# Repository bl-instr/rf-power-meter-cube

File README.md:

# RF Power Meter Cube

**Compact, wireless RF power measurement for distributed instrumentation and Blinky-Lite control-system deployments.**

| Enclosure | PCB |
|-----------|-----|
||

## Overview

The RF Power Meter Cube is a compact, wireless instrumentation module in the Blinky-Lite Instrumentation Platform. It is designed to measure RF power at or near the equipment being monitored, then communicate measurements and alarms to a central Blinky-Lite control system.

Built around the Raspberry Pi Pico W / RP2040, the module uses 2.4 GHz Wi-Fi and MQTT publish/subscribe communication. This event-driven approach supports distributed deployments without wired data connections and enables Blinky-Lite to use device information for recording, notifications, visualisation, and machine-protection workflows.

### Key features

- Purpose-built function: Dedicated RF power measurement using the Mini-Circuits ZX47-40LN-S+ logarithmic RF power detector.
- Compact deployment: DIN Mod3-compatible enclosure with a removable DIN-rail mount for space-constrained installations.
- Wireless connectivity: 2.4 GHz Wi-Fi for remote or distributed installations.
- Event-driven integration: MQTT publish/subscribe communication with Blinky-Lite.
- Fast alarm and state reporting: RF power exceeding or falling below configured limits can be reported immediately.
- Configurable operation: Using the Blinky-Lite control system, calibration constants can be adjusted easily for each device and its particular frequency band.
- Open-source firmware: Microcontroller code can be adapted for site-specific instrumentation and integration requirements.

## Technical summary

| Specification | Details |
|---------------|---------|
| Primary function | RF power measurement |
| Sensor / interface | Mini-Circuits ZX47-40LN-S+ RF power detector |
| Channels | One RF measurement channel |
| Measurement / operating range | 10 MHz to 8 GHz; 60 dB dynamic range (−40 dBm to +20 dBm) |
| Inputs / outputs | SMA male RF input |
| Power input | 5 V DC via 2.1 mm barrel connector |
| Wireless | 2.4 GHz Wi-Fi |
| Communication | MQTT publish/subscribe protocol |
| Controller | Raspberry Pi Pico W / RP2040 |
| PCB dimensions | 48 mm × 86 mm |
| Enclosure and mounting | 58 mm × 96 mm × 28 mm; DIN Mod3-compatible enclosure with removable DIN-rail mount |
| Platform | Blinky-Lite Instrumentation Platform |

### Typical applications

- RF system commissioning and troubleshooting
- Continuous RF power monitoring at remote equipment locations
- Accelerator, laboratory, and industrial test systems
- Distributed instrumentation installations requiring central visibility
- RF alarm and machine-protection workflows

## Getting started

### Hardware

1. Install the RF Power Meter Cube near the RF point to be monitored.
2. Connect the RF signal to the SMA input, ensuring the expected input level and frequency remain within the supported measurement range.
3. Verify that the RF source, connector, cabling, and installation conditions are suitable for the application.
4. Power the device from a regulated 5 V DC supply through the 2.1 mm barrel connector.
5. Mount the enclosure on a DIN rail when required, or remove the DIN-rail mount for an alternative installation.

### Firmware build target

The firmware targets the Raspberry Pi Pico W / RP2040 using the Arduino-Pico board support.
- Board: Pico W / RP2040-compatible target
- Flash layout: Sketch 1920 KB, filesystem 128 KB
- FQBN flash option: flash=2097152_131072

### Open-source software and licensing

The firmware is released under the MIT License, giving users broad permission to study, modify, and adapt the code for their own applications. The open hardware design can likewise be customised to suit site-specific requirements. The firmware uses the open-source Arduino-BlinkyPicoW library, which is also available under the MIT License.

### Configuration

1. Build and upload the firmware using the project’s source and configuration files.
2. Use the onboard web interface to set or update Wi-Fi credentials.
3. Configure the MQTT connection and create the corresponding device integration in Blinky-Lite.
4. Set calibration data and measurement limits appropriate to the RF detector, operating frequency, and required accuracy.
5. Verify that normal measurements and alarm events appear as expected in Blinky-Lite.

### Integration model

The RF Power Meter Cube uses MQTT to publish measurements and alarm events. This event-driven model avoids conventional polling and enables prompt control-system responses to changing RF conditions.

In a typical deployment, the device connects by Wi-Fi to the network and communicates through an MQTT broker. Blinky-Lite represents it as an integrated instrumentation node and can use its information for recording, display, notification, alarms, and machine-protection logic.

### Measurement, safety, and installation considerations

- Confirm that connected RF signals and environmental conditions are within the product’s specified limits.
- Apply calibration and measurement limits appropriate to the intended frequency band and required accuracy.
- Validate normal operation and alarm behaviour against a known reference source before relying on the device for operational or protection decisions.
- Review connector, cable, grounding, shielding, enclosure, and environmental requirements before installation.
- Do not exceed the supported RF input range.

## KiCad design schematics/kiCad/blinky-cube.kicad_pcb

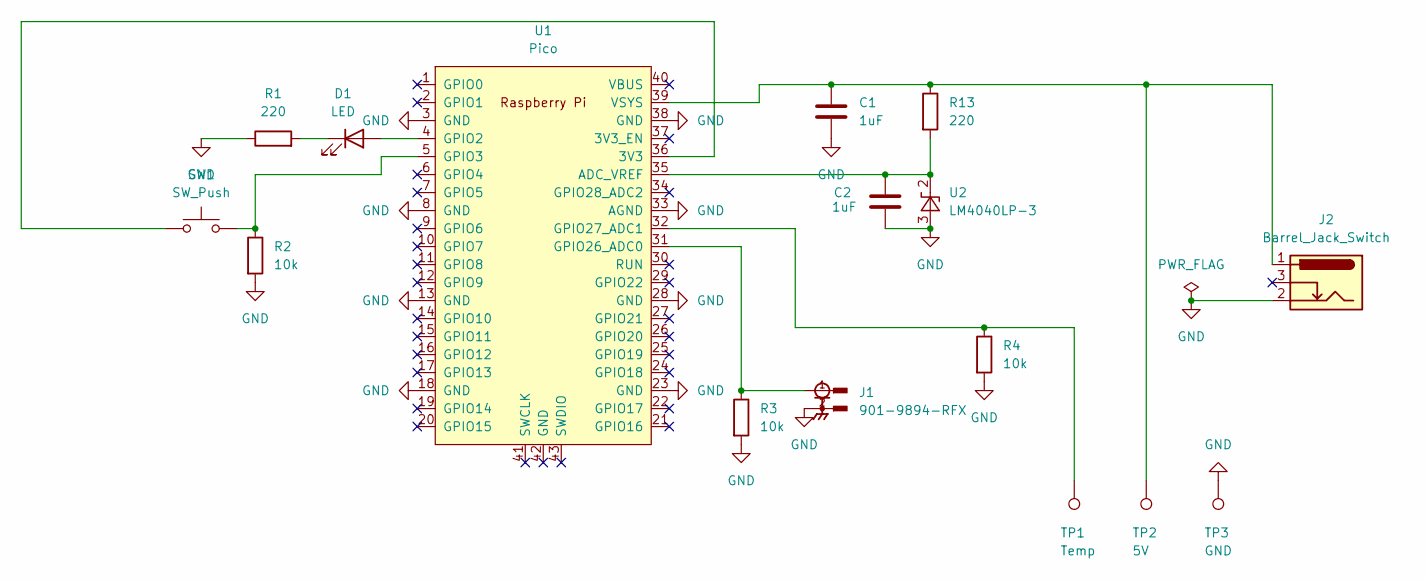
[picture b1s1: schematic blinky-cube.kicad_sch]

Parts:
C1, C2: 1uF; C_Disc_D4.7mm_W2.5mm_P5.00mm
D1: LED; LED_D5.0mm
J1: 901-9894-RFX; AMPHENOL_901-9894-RFX; PARTREV A
J2: Barrel_Jack_Switch; BarrelJack_HorizontalNC
R1, R13: 220; R_Axial_DIN0207_L6.3mm_D2.5mm_P7.62mm_Horizontal
R2, R3, R4: 10k; R_Axial_DIN0207_L6.3mm_D2.5mm_P7.62mm_Horizontal
SW1: SW_Push; SW_PUSH_6mm
TP1: Temp; TestPoint_THTPad_D2.0mm_Drill1.0mm
TP2: 5V; TestPoint_THTPad_D2.0mm_Drill1.0mm
TP3: GND; TestPoint_THTPad_D2.0mm_Drill1.0mm
U1: Pico; RPi_Pico_SMD_TH
U2: LM4040LP-3; TO-92_Inline

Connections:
GND: C1.2, C2.2, J1.2, J1.3, J1.4, J1.5, J2.2, R1.1, R2.2, R3.2, R4.2, TP3.1 (1_1), U1.3 (GND), U1.8 (GND), U1.13 (GND), U1.18 (GND), U1.23 (GND), U1.28 (GND), U1.33 (AGND), U1.38 (GND), U2.3 (A)
unnamed: D1.2 (A), U1.4 (GPIO2)
unnamed: D1.1 (K), R1.2
unnamed: SW1.1, U1.36 (3V3)
unnamed: C2.1, R13.2, U1.35 (ADC_VREF), U2.2 (K)
unnamed: R2.1, SW1.2, U1.5 (GPIO3)
unnamed: J1.1, R3.1, U1.31 (GPIO26_ADC0)
unnamed: R4.1, TP1.1 (1_1), U1.32 (GPIO27_ADC1)
unnamed: C1.1, J2.1, R13.1, TP2.1 (1_1), U1.39 (VSYS)

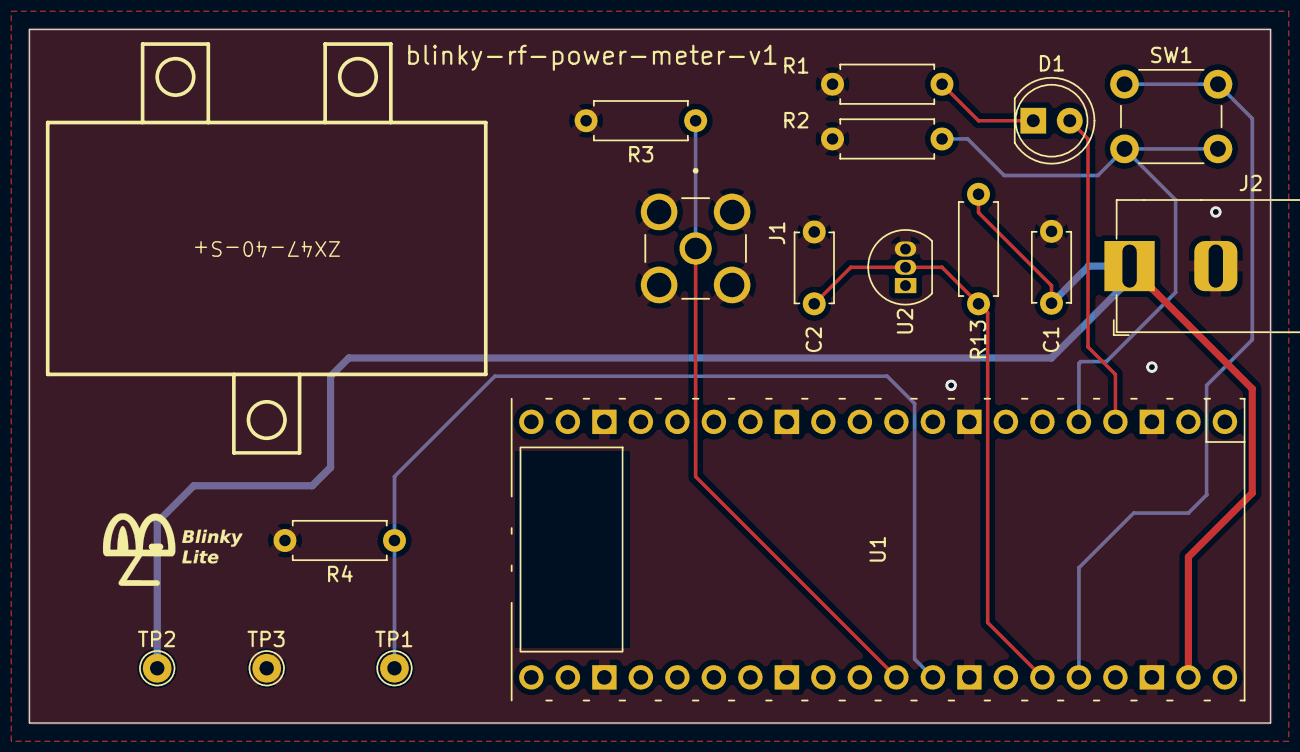
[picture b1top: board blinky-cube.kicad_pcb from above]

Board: 2 copper layers, 86.4 x 48.3 mm, 16 parts (0 on the bottom side), 9 nets.
